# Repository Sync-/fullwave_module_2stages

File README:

This is a stackable fullwave multiplier based around Wima MKP/FKP capacitors and cheap HV diodes

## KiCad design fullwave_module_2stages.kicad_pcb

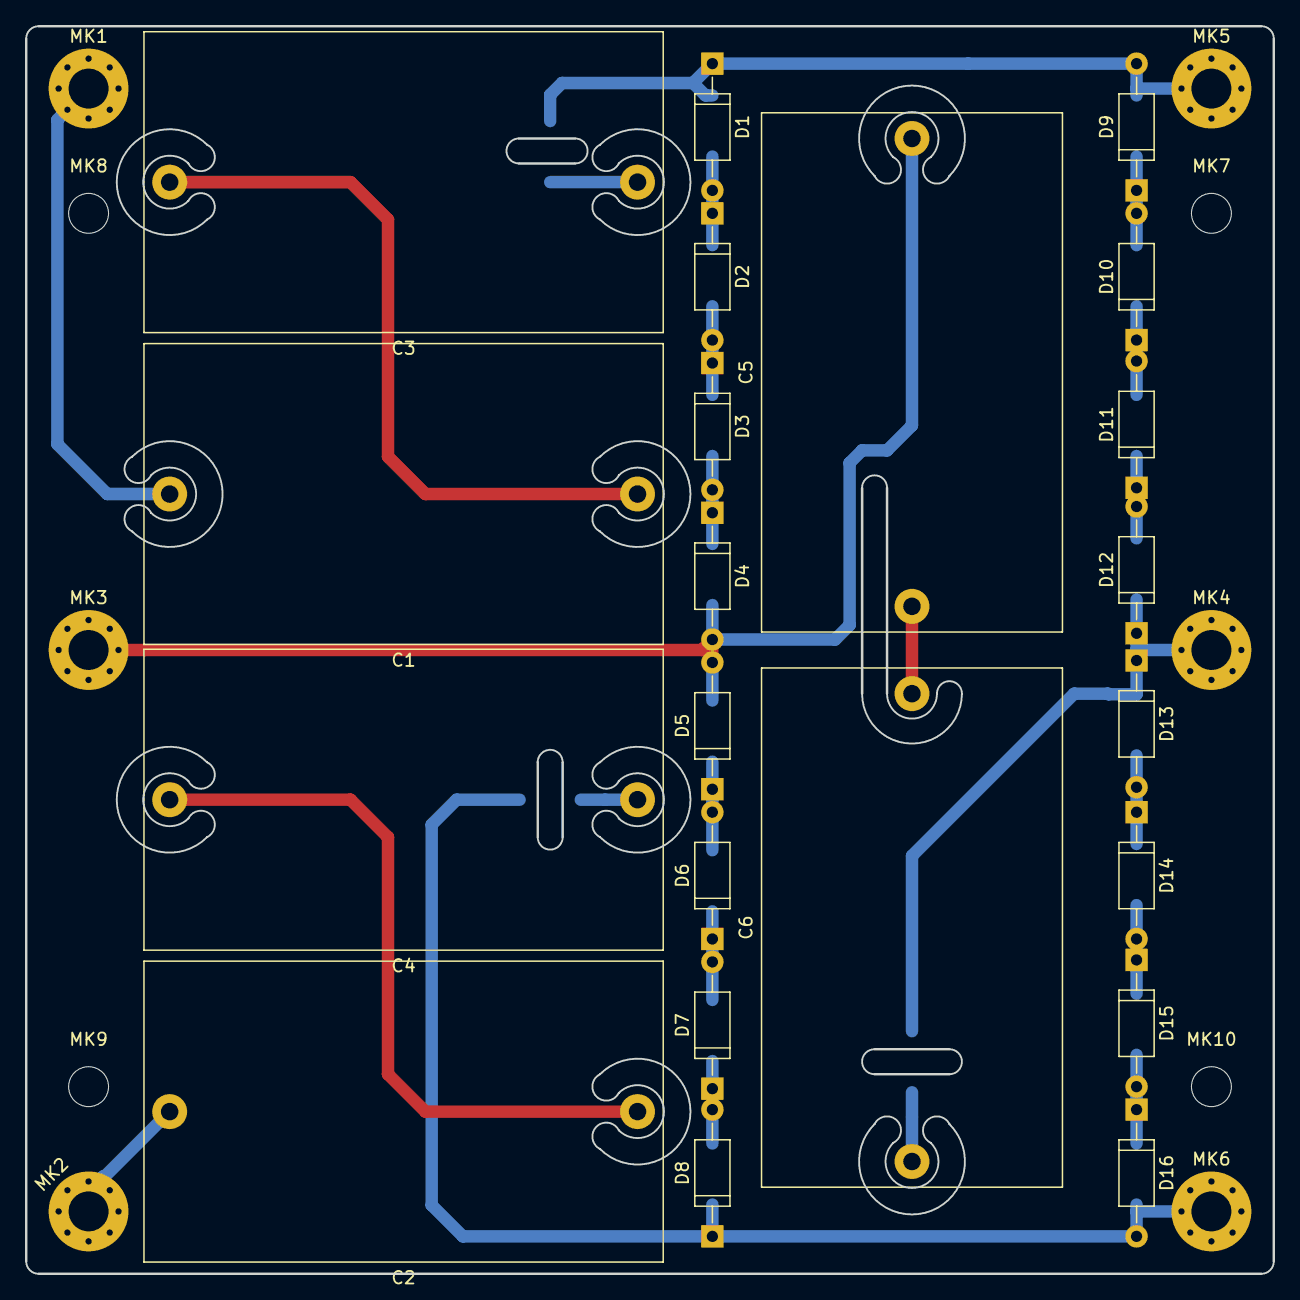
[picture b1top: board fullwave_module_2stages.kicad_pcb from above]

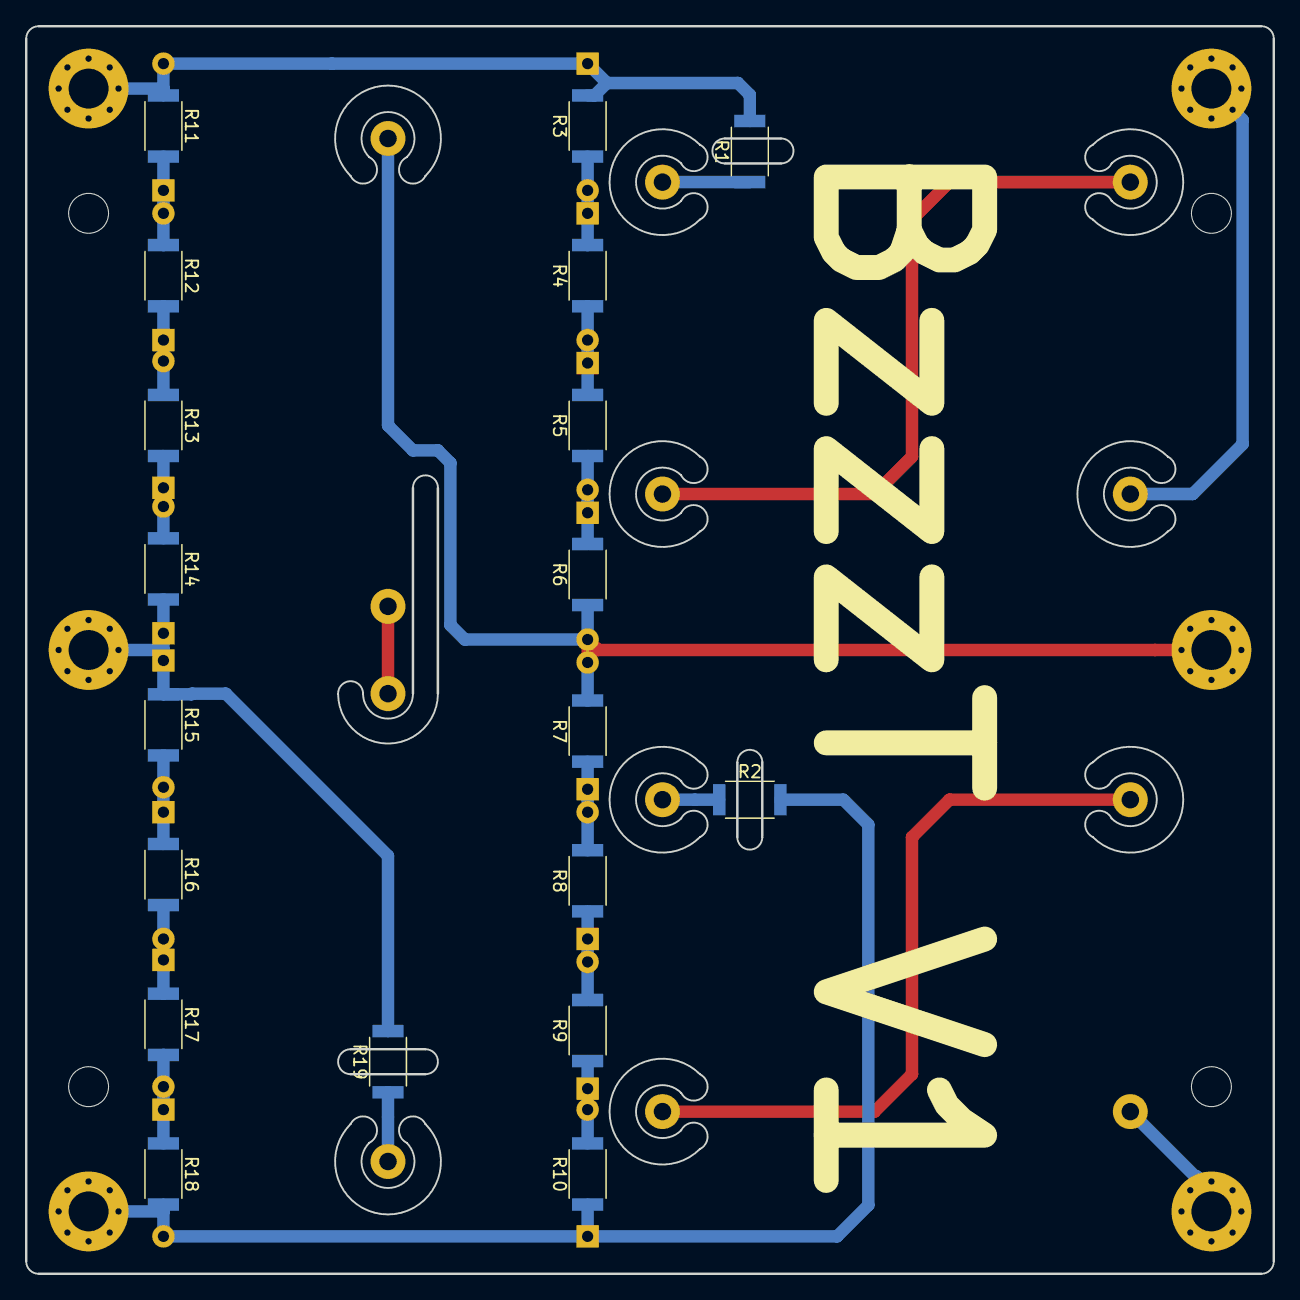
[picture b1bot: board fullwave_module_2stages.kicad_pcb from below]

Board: 2 copper layers, 100.0 x 100.0 mm, 51 parts (19 on the bottom side), 24 nets.

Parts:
C1, C2, C3, C4, C5, C6: C; C_Rect_L41.5mm_W24.0mm_P37.50mm_MKS4
D1, D2, D3, D4, D5, D6, D7, D8, D9, D10, D11, D12, D13, D14, D15, D16: D; D_A-405_P10.16mm_Horizontal
MK1, MK2, MK3, MK4, MK5, MK6: Mounting_Hole_PAD; MountingHole_3.2mm_M3_Pad_Via
MK7, MK8, MK9, MK10: Mounting_Hole; MountingHole_3.2mm_M3_DIN965
R1, R2, R19: 330; R_2010
R3, R4, R5, R6, R7, R8, R9, R10, R11, R12, R13, R14, R15, R16, R17, R18: 3.3M; R_2010

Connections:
unnamed: C1.1, C3.2
unnamed: C1.2, MK1.1
unnamed: C2.1, C4.2
unnamed: C2.2, MK2.1
unnamed: C3.1, R1.1
unnamed: C4.1, R2.1
unnamed: C5.1, C6.2
unnamed: C5.2, D4.2, D5.2, MK3.1, R6.1, R7.2
unnamed: C6.1, R19.1
unnamed: D1.1, D9.2, MK5.1, R1.2, R3.2, R11.1
unnamed: D1.2, D2.1, R3.1, R4.2
unnamed: D2.2, D3.1, R4.1, R5.2
unnamed: D3.2, D4.1, R5.1, R6.2
unnamed: D5.1, D6.2, R7.1, R8.2
unnamed: D6.1, D7.2, R8.1, R9.2
unnamed: D7.1, D8.2, R9.1, R10.2
unnamed: D10.1, D11.2, R12.2, R13.1
unnamed: D9.1, D10.2, R11.2, R12.1
unnamed: D11.1, D12.2, R13.2, R14.1
unnamed: D12.1, D13.1, MK4.1, R14.2, R15.1, R19.2
unnamed: D13.2, D14.1, R15.2, R16.1
unnamed: D14.2, D15.1, R16.2, R17.1
unnamed: D15.2, D16.1, R17.2, R18.1
unnamed: D8.1, D16.2, MK6.1, R2.2, R10.1, R18.2

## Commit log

2019-01-04 completed module
2019-01-04 add readme
